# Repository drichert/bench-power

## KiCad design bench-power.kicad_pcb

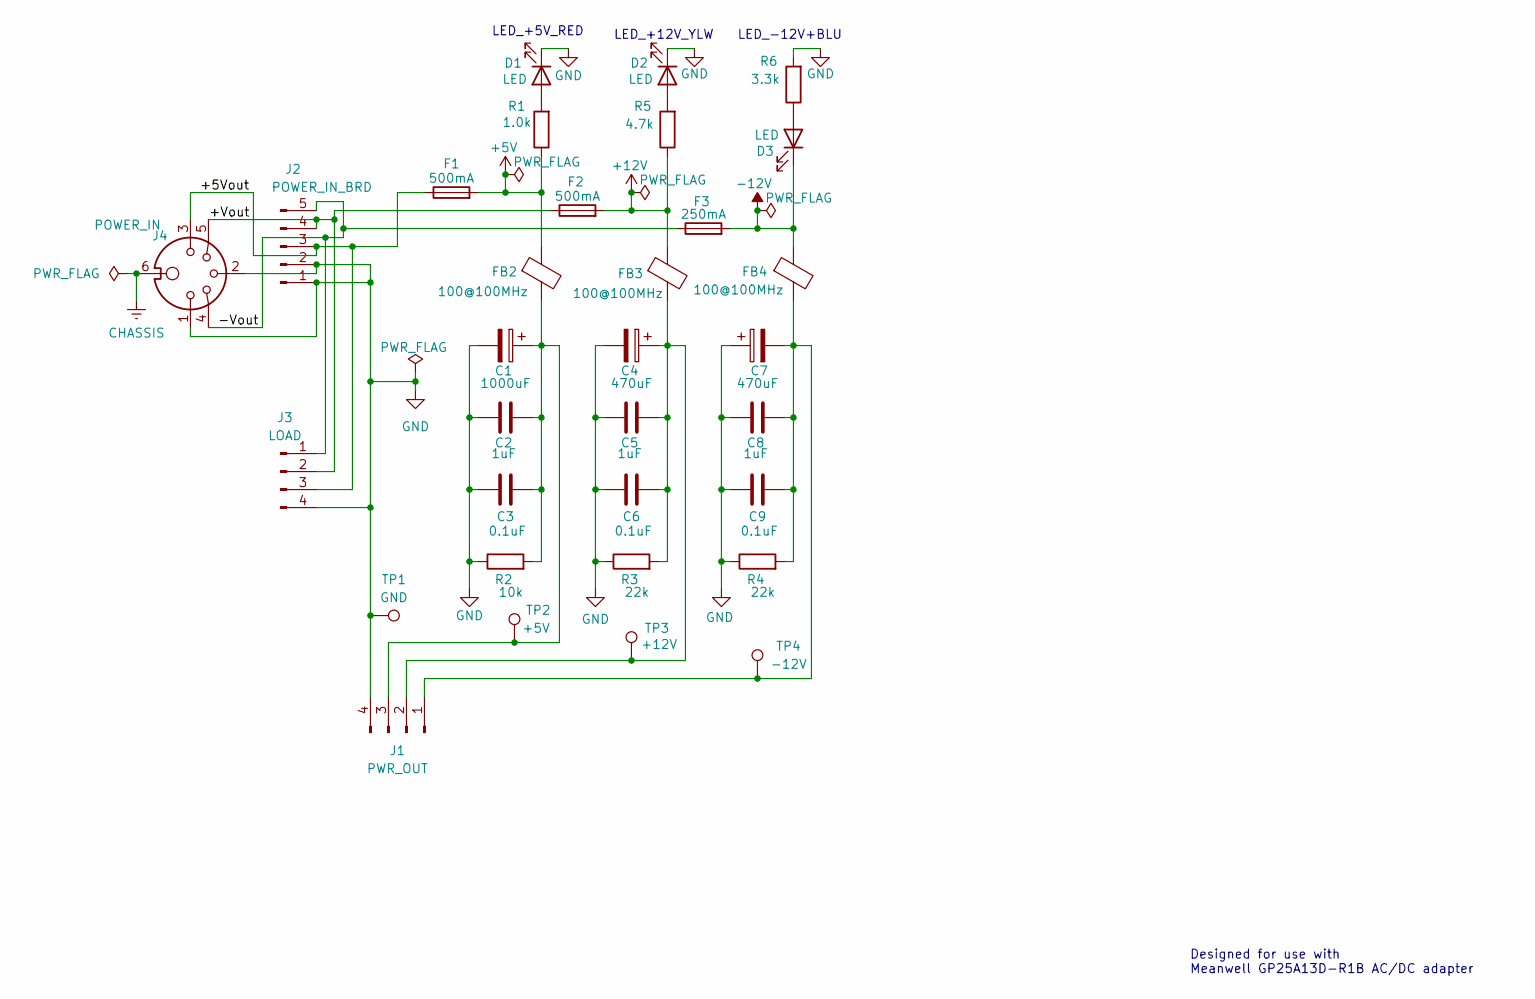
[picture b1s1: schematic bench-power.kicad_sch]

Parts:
C1: 1000uF; CP_Radial_D10.0mm_P5.00mm
C2, C5, C8: 1uF; C_Rect_L7.2mm_W4.5mm_P5.00mm_FKS2_FKP2_MKS2_MKP2
C3, C6, C9: 0.1uF; C_Rect_L4.0mm_W2.5mm_P2.50mm
C4, C7: 470uF; CP_Radial_D10.0mm_P5.00mm
D1, D2, D3: LED; LED_D5.0mm
F1, F2: 500mA; 696101000002
F3: 250mA; 696101000002
FB2, FB3, FB4: 100@100MHz; L_Axial_L5.3mm_D2.2mm_P7.62mm_Horizontal_Vishay_IM-1
J1: PWR_OUT; JST_XH_B4B-XH-A_1x04_P2.50mm_Vertical
J2: POWER_IN_BRD; JST_XH_B5B-XH-A_1x05_P2.50mm_Vertical
J3: LOAD; JST_XH_B4B-XH-A_1x04_P2.50mm_Vertical
J4: POWER_IN
R1: 1.0k; R_Axial_DIN0204_L3.6mm_D1.6mm_P5.08mm_Horizontal
R2: 10k; R_Axial_DIN0204_L3.6mm_D1.6mm_P5.08mm_Horizontal
R3, R4: 22k; R_Axial_DIN0204_L3.6mm_D1.6mm_P5.08mm_Horizontal
R5: 4.7k; R_Axial_DIN0204_L3.6mm_D1.6mm_P5.08mm_Horizontal
R6: 3.3k; R_Axial_DIN0204_L3.6mm_D1.6mm_P5.08mm_Horizontal
TP1: GND; TestPoint_Pad_D1.0mm
TP2: +5V; TestPoint_Pad_D1.0mm
TP3: +12V; TestPoint_Pad_D1.0mm
TP4: -12V; TestPoint_Pad_D1.0mm

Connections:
+5V: F1.2, FB2.1, R1.1
+12V: F2.2, FB3.1, R5.1
-12V: D3.1 (K), F3.2, FB4.1
/+5Vout: F1.1, J2.3, J3.3, J4.3 (+5V)
/+Vout: F2.1, J2.4, J3.2, J4.5 (+12V)
/-Vout: F3.1, J2.5, J3.1, J4.4 (-12V)
GND: C1.2, C2.1, C3.1, C4.2, C5.1, C6.1, C7.1, C8.1, C9.1, D1.1 (K), D2.1 (K), J1.4, J2.1, J2.2, J3.4, J4.1 (COM), J4.2 (COM), R2.1, R3.1, R4.1, R6.2, TP1.1
unnamed: D1.2 (A), R1.2
unnamed: D2.2 (A), R5.2
unnamed: D3.2 (A), R6.1
unnamed: C7.2, C8.2, C9.2, FB4.2, J1.1, R4.2, TP4.1
unnamed: C4.1, C5.2, C6.2, FB3.2, J1.2, R3.2, TP3.1
unnamed: C1.1, C2.2, C3.2, FB2.2, J1.3, R2.2, TP2.1

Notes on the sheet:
LED_-12V+BLU
LED_+12V_YLW
Designed for use with Meanwell GP25A13D-R1B AC/DC adapter
LED_+5V_RED

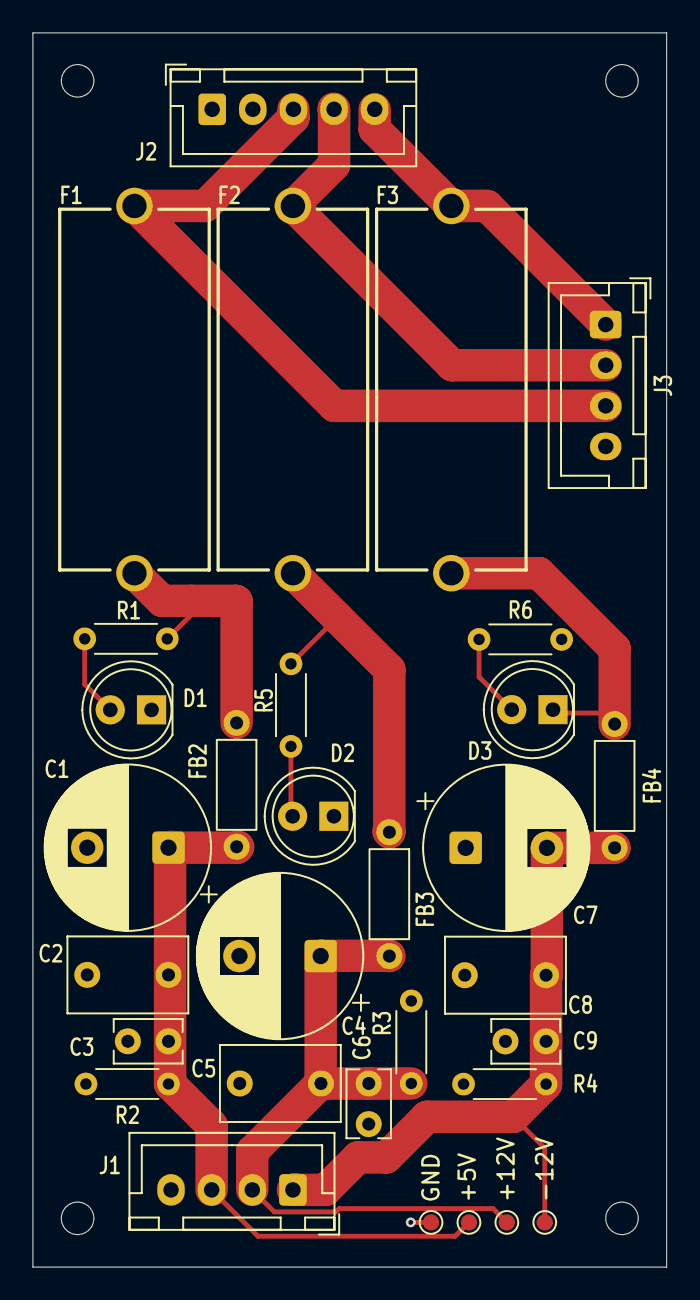
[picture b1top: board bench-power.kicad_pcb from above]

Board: 2 copper layers, 39.0 x 76.0 mm, 31 parts (0 on the bottom side), 13 nets.

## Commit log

2026-02-12 update power symobl
2026-02-12 banana jack output
2026-02-22 prototype candidate
2026-02-22 wip pre-fab tweaks, ignore lockfiles
2026-02-22 flip silkscreen, Lato font
2026-02-23 test points
2026-02-25 pre-move fuseholders/load jack
2026-02-25 shuffle jst connectors
